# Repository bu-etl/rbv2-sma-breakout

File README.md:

# rbv2-sma-breakout

Folder contains the breakout board pcb design and schematic.

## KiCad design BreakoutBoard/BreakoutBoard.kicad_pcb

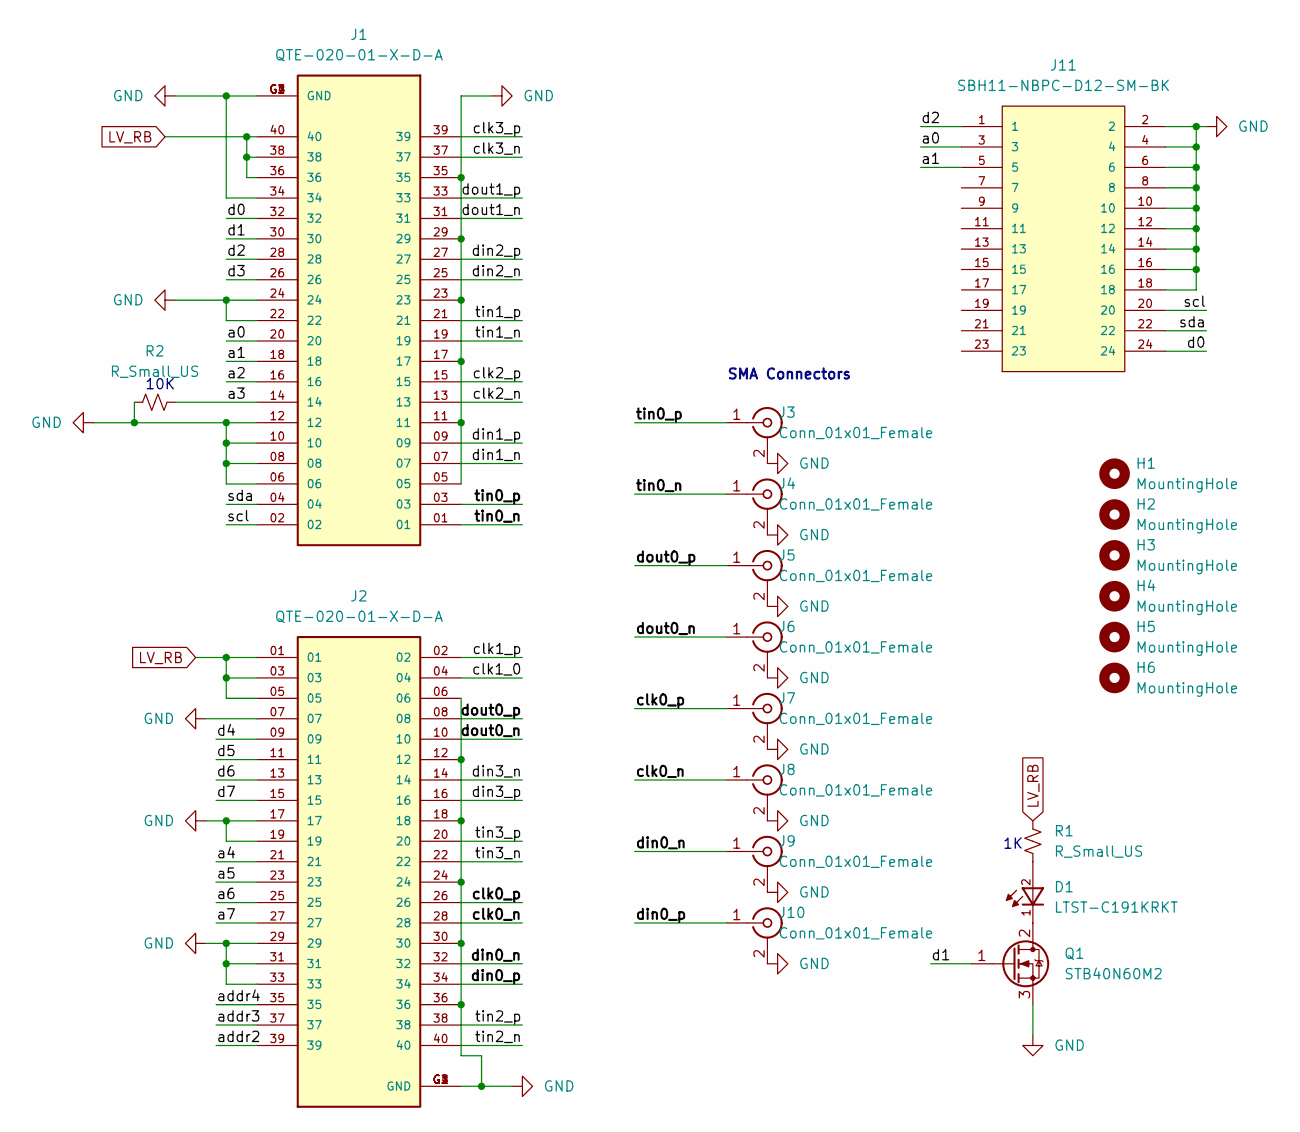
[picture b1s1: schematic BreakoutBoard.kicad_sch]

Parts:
D1: LTST-C191KRKT; 0603
H1, H2, H3, H4, H5, H6: MountingHole; MountingHole_2.5mm
J1, J2: QTE-020-01-X-D-A; SAMTEC_QTE-020-01-X-D-A; PARTREV K
J3, J4, J5, J6, J7, J8, J9, J10: Conn_01x01_Female; SMA_Amphenol_901-143_Horizontal
J11: SBH11-NBPC-D12-SM-BK; SULLINS_SBH11-NBPC-D12-SM-BK; PARTREV H
Q1: STB40N60M2; TRANS_MMBT2907A
R1, R2: R_Small_US; R_0603_1608Metric

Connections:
/a0: J1.20, J11.3
/a1: J1.18, J11.5
/a2: J1.16
/a3: J1.14, R2.2
/a4: J2.21
/a5: J2.23
/a6: J2.25
/a7: J2.27
/addr2: J2.39
/addr3: J2.37
/addr4: J2.35
/clk0_n: J2.28, J8.1 (In)
/clk0_p: J2.26, J7.1 (In)
/clk1_0: J2.04
/clk1_p: J2.02
/clk2_n: J1.13
/clk2_p: J1.15
/clk3_n: J1.37
/clk3_p: J1.39
/d0: J1.32, J11.24
/d1: J1.30, Q1.1 (G)
/d2: J1.28, J11.1
/d3: J1.26
/d4: J2.09
/d5: J2.11
/d6: J2.13
/d7: J2.15
/din0_n: J2.32, J9.1 (In)
/din0_p: J2.34, J10.1 (In)
/din1_n: J1.07
/din1_p: J1.09
/din2_n: J1.25
/din2_p: J1.27
/din3_n: J2.14
/din3_p: J2.16
/dout0_n: J2.10, J6.1 (In)
/dout0_p: J2.08, J5.1 (In)
/dout1_n: J1.31
/dout1_p: J1.33
/scl: J1.02, J11.20
/sda: J1.04, J11.22
/tin0_n: J1.01, J4.1 (In)
/tin0_p: J1.03, J3.1 (In)
/tin1_n: J1.19
/tin1_p: J1.21
/tin2_n: J2.40
/tin2_p: J2.38
/tin3_n: J2.22
/tin3_p: J2.20
GND: J1.05, J1.06, J1.08, J1.10, J1.11, J1.12, J1.17, J1.22, J1.23, J1.24, J1.29, J1.34, J1.35, J1.G1 (GND), J1.G2 (GND), J1.G3 (GND), J1.G4 (GND), J2.06, J2.07, J2.12, J2.17, J2.18, J2.19, J2.24, J2.29, J2.30, J2.31, J2.33, J2.36, J2.G1 (GND), J2.G2 (GND), J2.G3 (GND), J2.G4 (GND), J3.2 (Ext), J4.2 (Ext), J5.2 (Ext), J6.2 (Ext), J7.2 (Ext), J8.2 (Ext), J9.2 (Ext), J10.2 (Ext), J11.2, J11.4, J11.6, J11.8, J11.10, J11.12, J11.14, J11.16, J11.18, Q1.3 (S), R2.1
LV_RB: J1.36, J1.38, J1.40, J2.01, J2.03, J2.05, R1.1
unnamed: D1.1, Q1.2 (D)
unnamed: D1.2, R1.2

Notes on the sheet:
SMA Connectors
10K

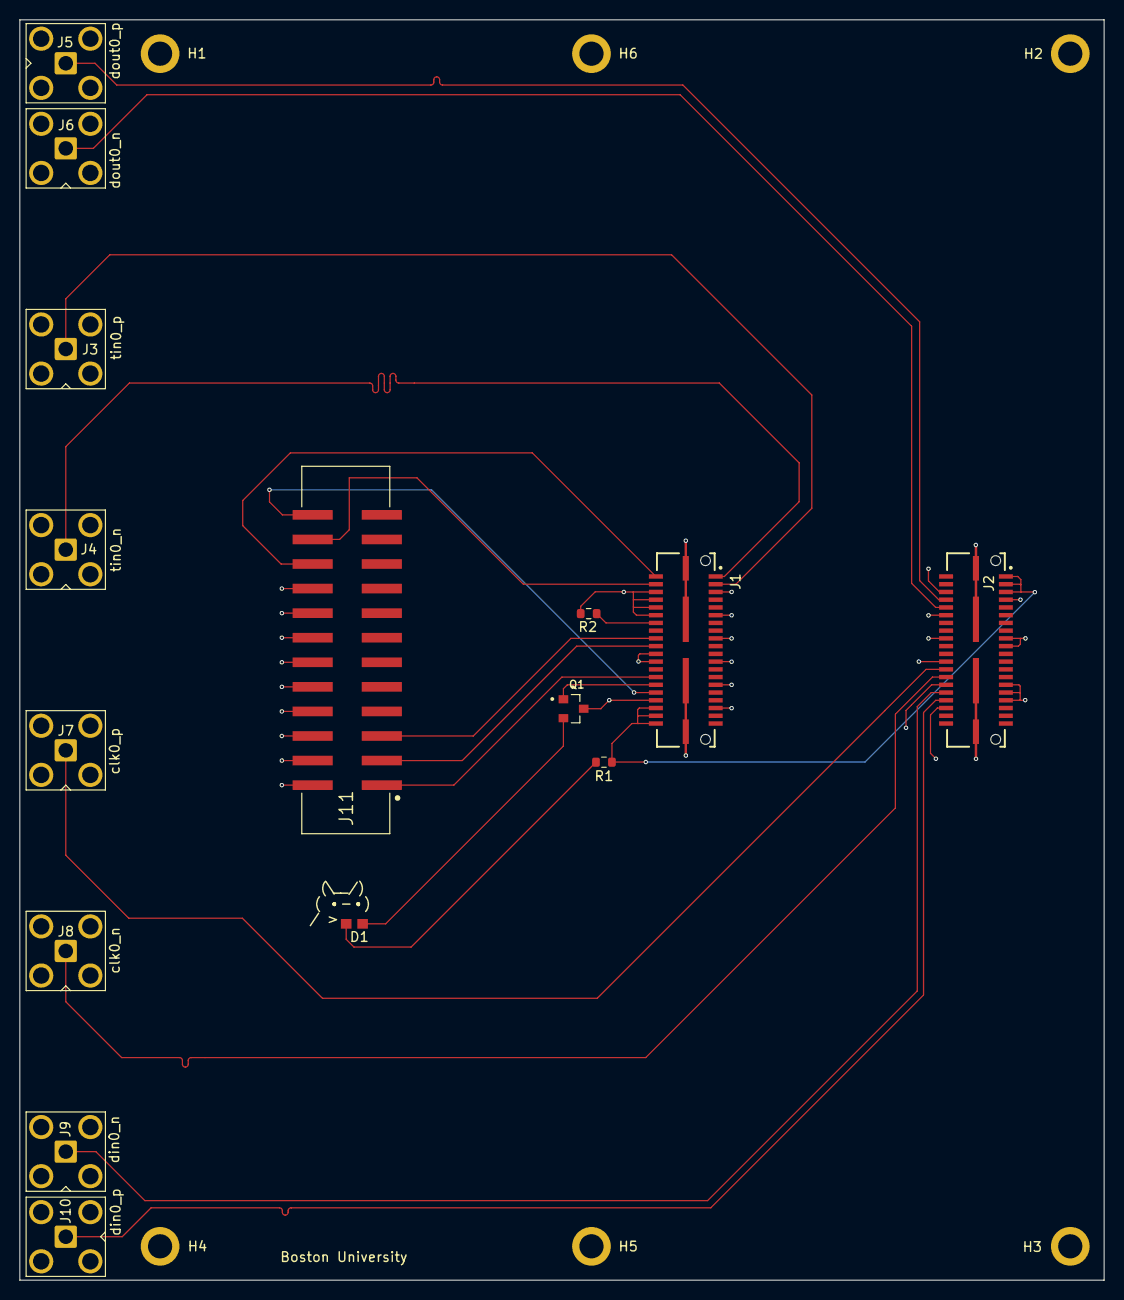
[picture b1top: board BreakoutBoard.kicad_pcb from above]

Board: 4 copper layers, 112.1 x 130.3 mm, 21 parts (0 on the bottom side), 20 nets.

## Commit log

2023-03-15 PCB files
2023-03-15 Breakout Board files
2023-03-15 Changed format
2023-03-19 Add files via upload
    Fixed GND
2023-03-19 Fixed issues
2023-03-21 Add files via upload
    Changed tracks and other minor fixes
2023-03-22 Add files via upload
    gerber files
